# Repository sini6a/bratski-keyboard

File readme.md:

# Bratski Keyboard

The Bratski Keyboard, named after the Slavic slang term "братски" meaning brother, is a compact mechanical keyboard powered by the Raspberry Pi Pico (RP2040) microcontroller. Designed with 44 soldered keys, it is optimized for seamless use with tablets, laptops, or smartphones. The keyboard boasts MX switches, renowned for their exceptional typing feel and durability, paired with custom resin-printed keycaps, delivering a distinctive and satisfying typing experience. Enhancing the overall robustness, the 3D-printed case, comprised of a main body and a back cover, completes the Bratski Keyboard's durable design.

## Project Structure

The project repository is structured as follows:

-   **`kicad/`**: Contains PCB design files and schematics.
-   **`gerbers/`**: Includes Gerber files essential for manufacturing.
-   **`case/`**: Consists of 3D print files for both the main body and the back cover of the keyboard.
-   **`firmware/`**: Incorporates a modified version of the KMK Firmware with custom key mappings.
-   **`keycaps/`**: MX Keycaps and modified version of the 3u keycap used on the keyboard.

## Pinout and Mapping

## Raspberry Pi Pico Firmware

To enable key mappings on the Raspberry Pi Pico, the Bratski Keyboard employs the KMK firmware. Follow these steps to set it up:

1. Install **[MicroPython](https://www.raspberrypi.com/documentation/microcontrollers/micropython.html)** from the official Raspberry Pi website.
2. Visit the official **[KMK](http://kmkfw.io/)** webpage, download the firmware, customize key mappings as per your preferences and pinouts, and install it on your Raspberry Pi.

_Note:_ If you prefer using the predefined key mappings provided in this repository, you can install the custom firmware available in the firmware folder.

## Keycaps

The Bratski keyboard features keycaps from the **[ConstantinoSchillebeeckx](https://github.com/ConstantinoSchillebeeckx/cherry-mx-keycaps)** collection. These keycaps, crafted using a resin printer, are compatible with MX switches. However, the keyboard supports all MX-compatible keycaps, providing users with flexibility in choosing and customizing their keycap sets.

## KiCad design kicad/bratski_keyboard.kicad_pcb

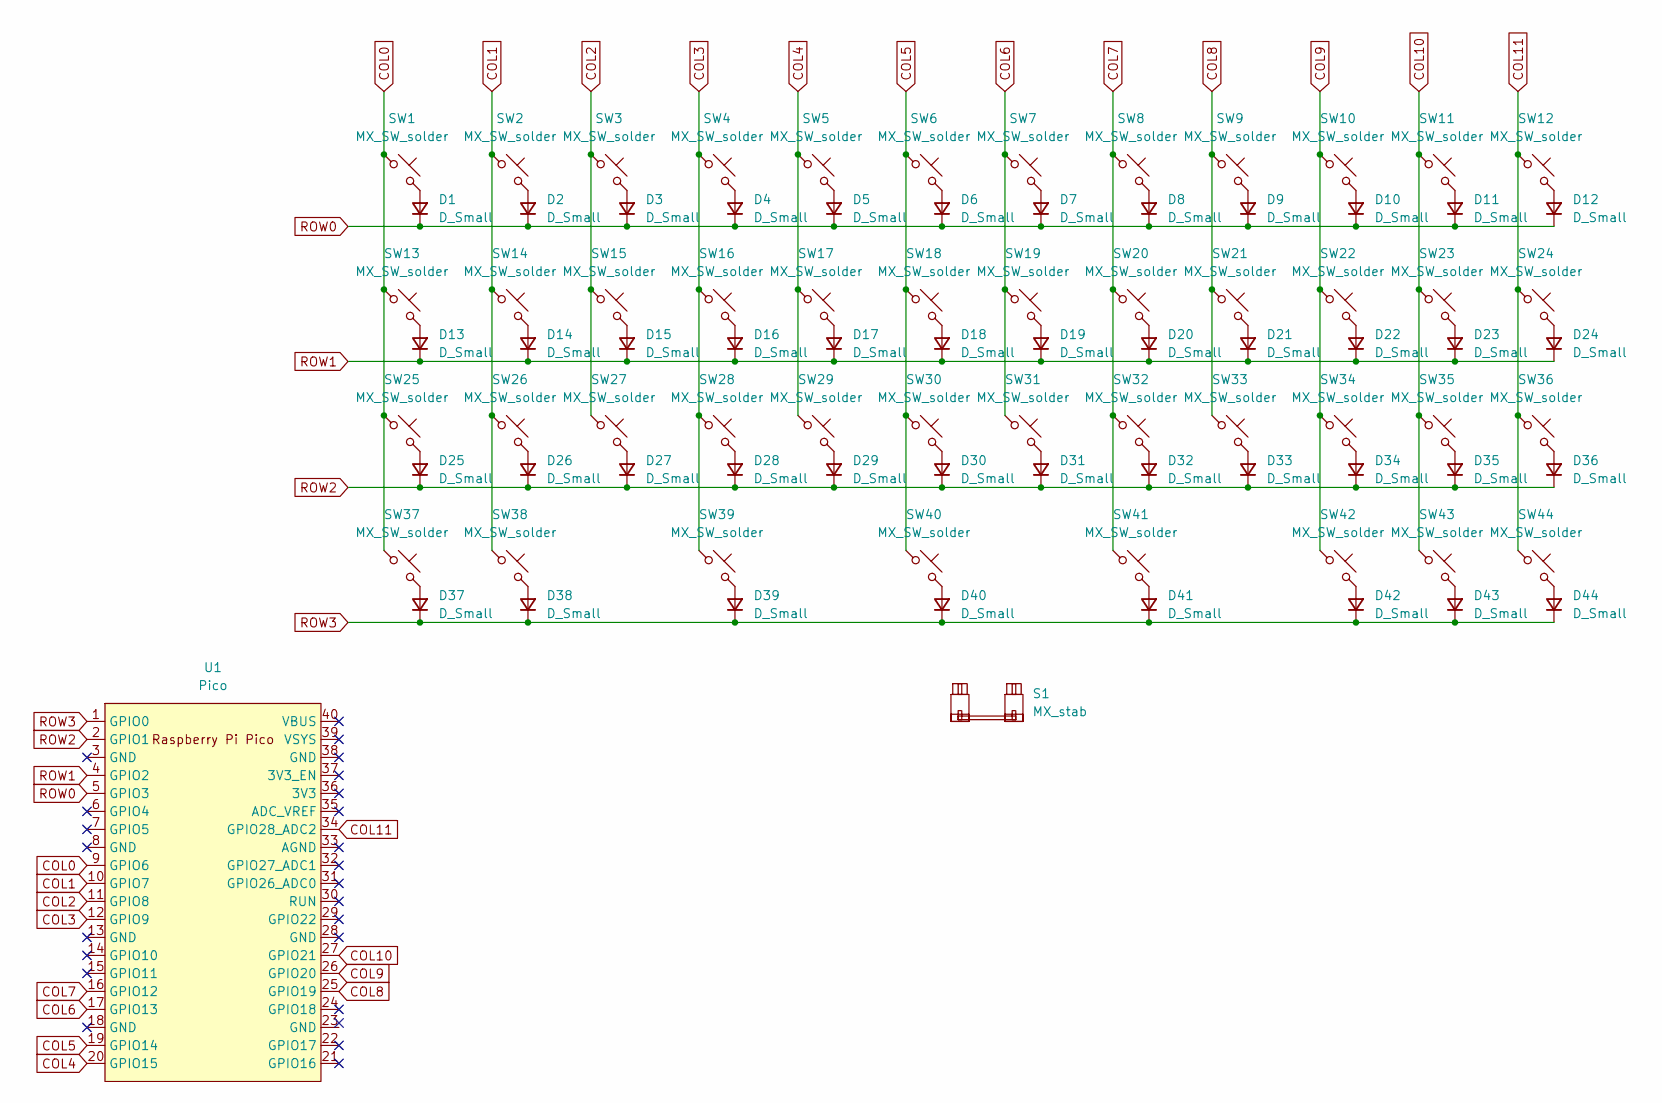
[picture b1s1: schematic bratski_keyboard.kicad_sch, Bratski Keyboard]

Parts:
D1, D2, D3, D4, D5, D6, D7, D8, D9, D10, D11, D12, D13, D14, D15, D16, D17, D18, D19, D20, D21, D22, D23, D24, D25, D26, D27, D28, D29, D30, D31, D32, D33, D34, D35, D36, D37, D38, D39, D40, D41, D42, D43, D44: D_Small; D_SOD-123
S1: MX_stab; STAB_MX_P_3u
SW1, SW2, SW3, SW4, SW5, SW6, SW7, SW8, SW9, SW10, SW11, SW13, SW14, SW15, SW16, SW17, SW18, SW19, SW20, SW21, SW22, SW23, SW26, SW27, SW28, SW29, SW30, SW31, SW32, SW33, SW34, SW35, SW40: MX_SW_solder; SW_MX_1u
SW12, SW24, SW37, SW39, SW41: MX_SW_solder; SW_MX_1.5u
SW25, SW36, SW38, SW42, SW43, SW44: MX_SW_solder; SW_MX_1.25u
U1: Pico; RPi_Pico_SMD_TH

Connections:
COL0: SW1.1, SW13.1, SW25.1, SW37.1, U1.9 (GPIO6)
COL1: SW2.1, SW14.1, SW26.1, SW38.1, U1.10 (GPIO7)
COL2: SW3.1, SW15.1, SW27.1, U1.11 (GPIO8)
COL3: SW4.1, SW16.1, SW28.1, SW39.1, U1.12 (GPIO9)
COL4: SW5.1, SW17.1, SW29.1, U1.20 (GPIO15)
COL5: SW6.1, SW18.1, SW30.1, SW40.1, U1.19 (GPIO14)
COL6: SW7.1, SW19.1, SW31.1, U1.17 (GPIO13)
COL7: SW8.1, SW20.1, SW32.1, SW41.1, U1.16 (GPIO12)
COL8: SW9.1, SW21.1, SW33.1, U1.25 (GPIO19)
COL9: SW10.1, SW22.1, SW34.1, SW42.1, U1.26 (GPIO20)
COL10: SW11.1, SW23.1, SW35.1, SW43.1, U1.27 (GPIO21)
COL11: SW12.1, SW24.1, SW36.1, SW44.1, U1.34 (GPIO28_ADC2)
unnamed: D1.2 (A), SW1.2
unnamed: D2.2 (A), SW2.2
unnamed: D3.2 (A), SW3.2
unnamed: D4.2 (A), SW4.2
unnamed: D5.2 (A), SW5.2
unnamed: D6.2 (A), SW6.2
unnamed: D7.2 (A), SW7.2
unnamed: D8.2 (A), SW8.2
unnamed: D9.2 (A), SW9.2
unnamed: D10.2 (A), SW10.2
unnamed: D11.2 (A), SW11.2
unnamed: D12.2 (A), SW12.2
unnamed: D13.2 (A), SW13.2
unnamed: D14.2 (A), SW14.2
unnamed: D15.2 (A), SW15.2
unnamed: D16.2 (A), SW16.2
unnamed: D17.2 (A), SW17.2
unnamed: D18.2 (A), SW18.2
unnamed: D19.2 (A), SW19.2
unnamed: D20.2 (A), SW20.2
unnamed: D21.2 (A), SW21.2
unnamed: D22.2 (A), SW22.2
unnamed: D23.2 (A), SW23.2
unnamed: D24.2 (A), SW24.2
unnamed: D25.2 (A), SW25.2
unnamed: D26.2 (A), SW26.2
unnamed: D27.2 (A), SW27.2
unnamed: D28.2 (A), SW28.2
unnamed: D29.2 (A), SW29.2
unnamed: D30.2 (A), SW30.2
unnamed: D31.2 (A), SW31.2
unnamed: D32.2 (A), SW32.2
unnamed: D33.2 (A), SW33.2
unnamed: D34.2 (A), SW34.2
unnamed: D35.2 (A), SW35.2
unnamed: D36.2 (A), SW36.2
unnamed: D37.2 (A), SW37.2
unnamed: D38.2 (A), SW38.2
unnamed: D39.2 (A), SW39.2
unnamed: D40.2 (A), SW40.2
unnamed: D41.2 (A), SW41.2
unnamed: D42.2 (A), SW42.2
unnamed: D43.2 (A), SW43.2
unnamed: D44.2 (A), SW44.2
ROW0: D1.1 (K), D2.1 (K), D3.1 (K), D4.1 (K), D5.1 (K), D6.1 (K), D7.1 (K), D8.1 (K), D9.1 (K), D10.1 (K), D11.1 (K), D12.1 (K), U1.5 (GPIO3)
ROW1: D13.1 (K), D14.1 (K), D15.1 (K), D16.1 (K), D17.1 (K), D18.1 (K), D19.1 (K), D20.1 (K), D21.1 (K), D22.1 (K), D23.1 (K), D24.1 (K), U1.4 (GPIO2)
ROW2: D25.1 (K), D26.1 (K), D27.1 (K), D28.1 (K), D29.1 (K), D30.1 (K), D31.1 (K), D32.1 (K), D33.1 (K), D34.1 (K), D35.1 (K), D36.1 (K), U1.2 (GPIO1)
ROW3: D37.1 (K), D38.1 (K), D39.1 (K), D40.1 (K), D41.1 (K), D42.1 (K), D43.1 (K), D44.1 (K), U1.1 (GPIO0)

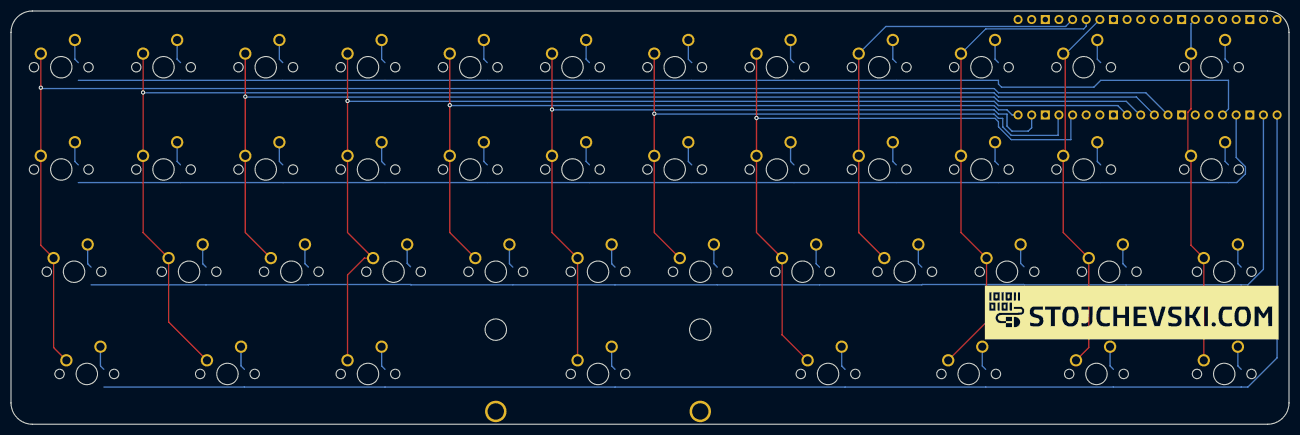
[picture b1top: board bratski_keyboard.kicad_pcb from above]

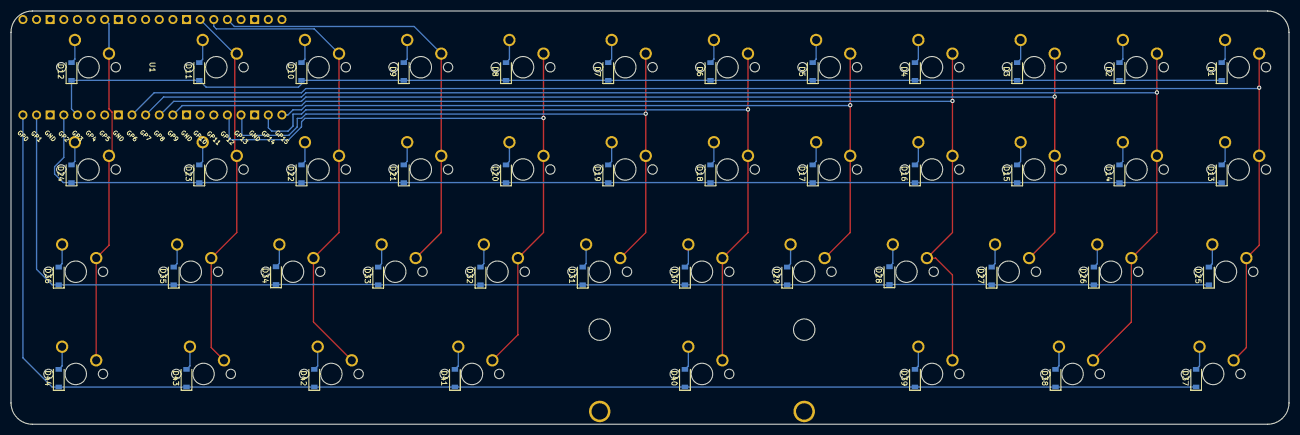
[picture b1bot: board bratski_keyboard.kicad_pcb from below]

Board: 2 copper layers, 238.1 x 77.0 mm, 90 parts (45 on the bottom side), 60 nets.

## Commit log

2024-02-13 revision 1
